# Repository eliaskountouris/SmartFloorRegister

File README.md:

# Smart Floor Register (Vent)

Developed alongside 2 mechanical engineering students. The MEs were responsible for designing the housing while I worked on the controller board. This was a prototype design and as such extra connectors and sensors were added they may not be used in the final version.

The controller board interfaces with 4 different thermocouples, which connect to Op-Amps to magnify the signal.

It also drives 2 motor controls (using I2C) and a servo (using PWM).

Power is driven by either batteries or a usb for debugging. A boost converter is on board to power the motors and servos.

## PCB Image

## Schematics

There is a schematic file (Schematic.pdf) detailing the workings of the controller board.

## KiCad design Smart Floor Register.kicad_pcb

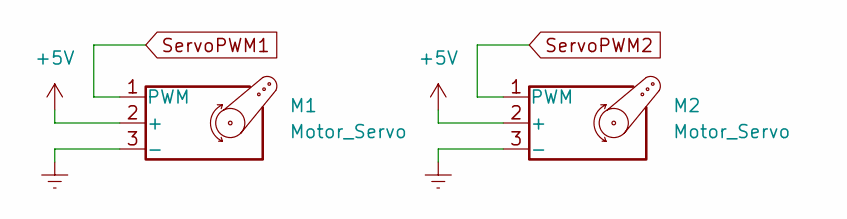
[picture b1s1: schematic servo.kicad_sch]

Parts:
M1, M2: Motor_Servo; Servo

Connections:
+5V: M1.2 (+), M2.2 (+); also elsewhere on the board
Earth: M1.3 (-), M2.3 (-); also elsewhere on the board
ServoPWM1: M1.1 (PWM); also elsewhere on the board
ServoPWM2: M2.1 (PWM); also elsewhere on the board

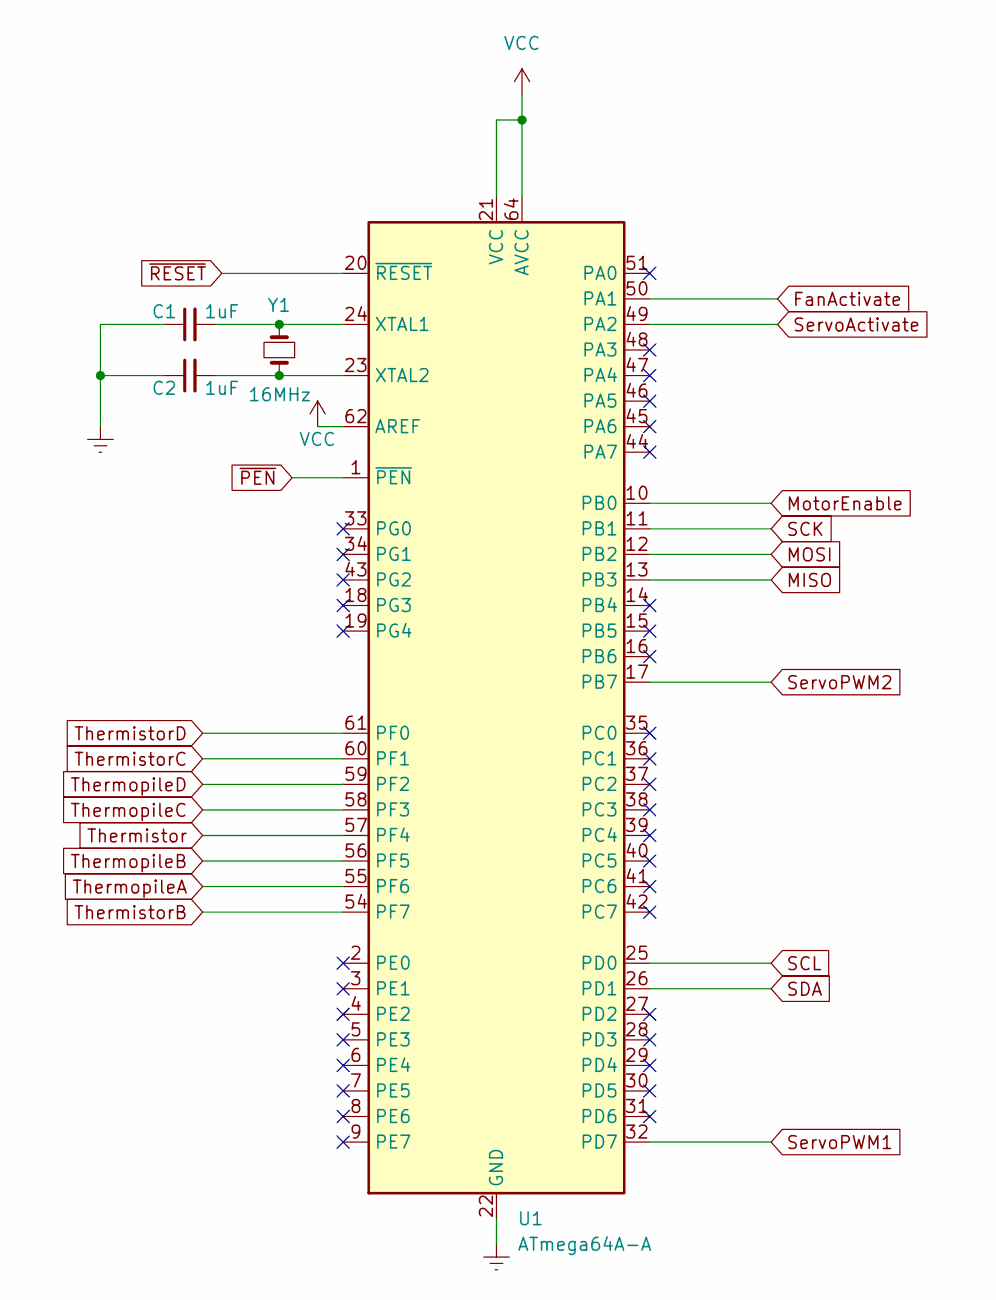
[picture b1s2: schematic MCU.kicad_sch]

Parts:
C1, C2: 1uF; R_0603_1608Metric_Pad0.98x0.95mm_HandSolder
U1: ATmega64A-A; TQFP-64_14x14mm_P0.8mm
Y1: 16MHz; XTAL_ECS-160-S-23A-TR

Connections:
Earth: C1.1, C2.1, U1.22 (GND), U1.53 (GND), U1.63 (GND); also elsewhere on the board
FanActivate: U1.50 (PA1); also elsewhere on the board
MISO: U1.13 (PB3); also elsewhere on the board
MOSI: U1.12 (PB2); also elsewhere on the board
MotorEnable: U1.10 (PB0); also elsewhere on the board
unnamed: C1.2, U1.24 (XTAL1), Y1.2
unnamed: C2.2, U1.23 (XTAL2), Y1.1
SCK: U1.11 (PB1); also elsewhere on the board
SCL: U1.25 (PD0); also elsewhere on the board
SDA: U1.26 (PD1); also elsewhere on the board
ServoActivate: U1.49 (PA2); also elsewhere on the board
ServoPWM1: U1.32 (PD7); also elsewhere on the board
ServoPWM2: U1.17 (PB7); also elsewhere on the board
Thermistor: U1.57 (PF4); also elsewhere on the board
ThermistorB: U1.54 (PF7); also elsewhere on the board
ThermistorC: U1.60 (PF1); also elsewhere on the board
ThermistorD: U1.61 (PF0); also elsewhere on the board
ThermopileA: U1.55 (PF6); also elsewhere on the board
ThermopileB: U1.56 (PF5); also elsewhere on the board
ThermopileC: U1.58 (PF3); also elsewhere on the board
ThermopileD: U1.59 (PF2); also elsewhere on the board
VCC: U1.21 (VCC), U1.52 (VCC), U1.62 (AREF), U1.64 (AVCC); also elsewhere on the board
~PEN: U1.1 (~PEN); also elsewhere on the board
~RESET: U1.20 (~RESET); also elsewhere on the board

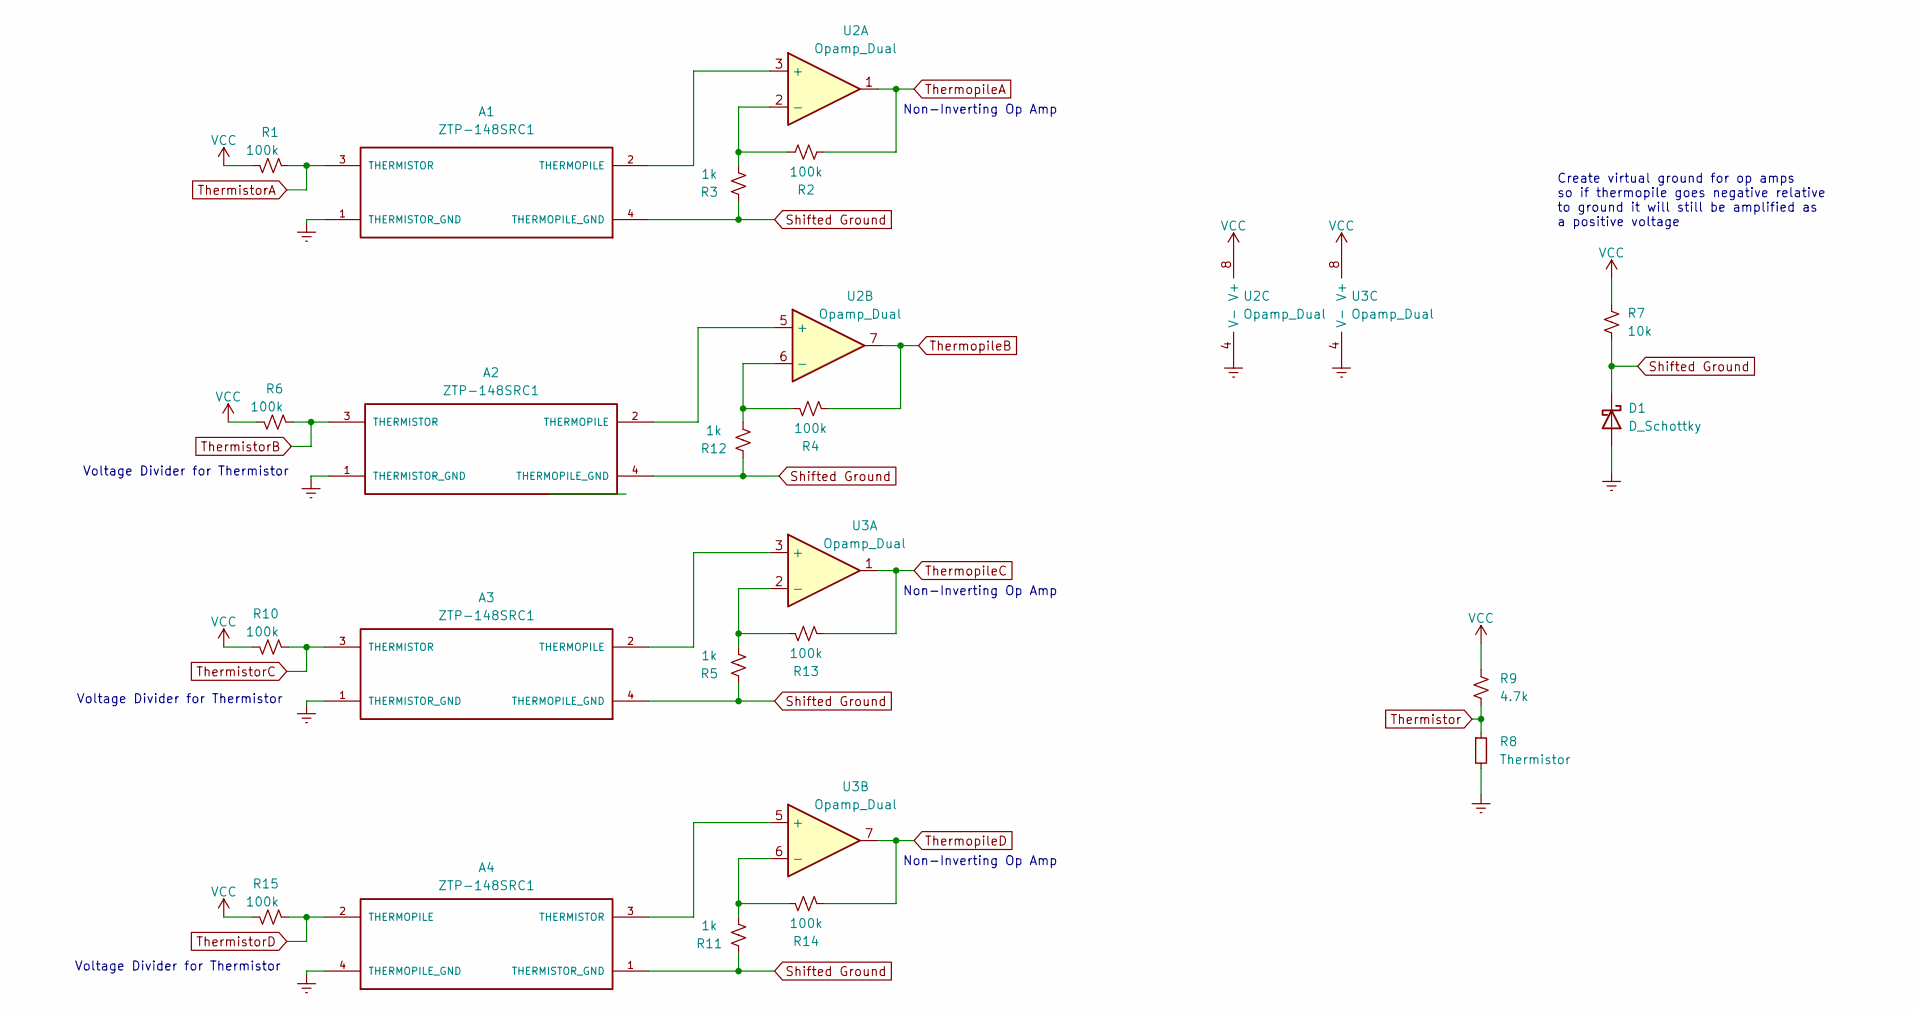
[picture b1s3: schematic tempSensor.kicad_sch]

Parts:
A1, A2, A3, A4: ZTP-148SRC1; Thermopile; PARTREV 07/2020
D1: D_Schottky; D_SOD-323
R1, R2, R4, R6, R10, R13, R14, R15: 100k; R_0603_1608Metric_Pad0.98x0.95mm_HandSolder
R3, R5, R11, R12: 1k; R_0603_1608Metric_Pad0.98x0.95mm_HandSolder
R7: 10k; R_0603_1608Metric_Pad0.98x0.95mm_HandSolder
R8: Thermistor; R_1206_3216Metric_Pad1.30x1.75mm_HandSolder
R9: 4.7k; R_0603_1608Metric_Pad0.98x0.95mm_HandSolder
U2, U3: Opamp_Dual; AD8539ARMZ-REEL

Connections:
Earth: A1.1 (THERMISTOR_GND), A2.1 (THERMISTOR_GND), A3.1 (THERMISTOR_GND), A4.4 (THERMOPILE_GND), D1.2 (A), R8.2, U2.4 (V-), U3.4 (V-); also elsewhere on the board
unnamed: A1.2 (THERMOPILE), U2.3 (+)
unnamed: A2.2 (THERMOPILE), U2.5 (+)
unnamed: A3.2 (THERMOPILE), U3.3 (+)
unnamed: A4.3 (THERMISTOR), U3.5 (+)
unnamed: R2.2, R3.2, U2.2 (-)
unnamed: R4.1, R12.2, U2.6 (-)
unnamed: R5.2, R13.1, U3.2 (-)
unnamed: R11.2, R14.1, U3.6 (-)
Shifted Ground: A1.4 (THERMOPILE_GND), A2.4 (THERMOPILE_GND), A3.4 (THERMOPILE_GND), A4.1 (THERMISTOR_GND), D1.1 (K), R3.1, R5.1, R7.2, R11.1, R12.1; also elsewhere on the board
Thermistor: R8.1, R9.2; also elsewhere on the board
ThermistorA: A1.3 (THERMISTOR), R1.2; also elsewhere on the board
ThermistorB: A2.3 (THERMISTOR), R6.2; also elsewhere on the board
ThermistorC: A3.3 (THERMISTOR), R10.2; also elsewhere on the board
ThermistorD: A4.2 (THERMOPILE), R15.2; also elsewhere on the board
ThermopileA: R2.1, U2.1; also elsewhere on the board
ThermopileB: R4.2, U2.7; also elsewhere on the board
ThermopileC: R13.2, U3.1; also elsewhere on the board
ThermopileD: R14.2, U3.7; also elsewhere on the board
VCC: R1.1, R6.1, R7.1, R9.1, R10.1, R15.1, U2.8 (V+), U3.8 (V+); also elsewhere on the board

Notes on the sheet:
Voltage Divider for Thermistor
Non-Inverting Op Amp
Create virtual ground for op amps so if thermopile goes negative relative to ground it will still be amplified as a positive voltage

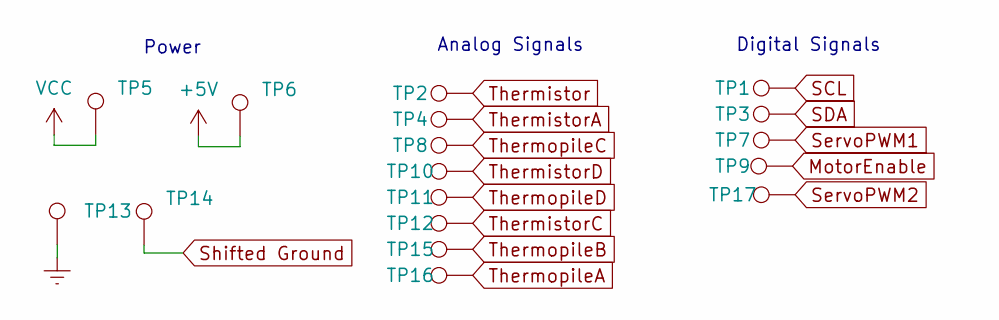
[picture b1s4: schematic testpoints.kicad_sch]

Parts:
TP1, TP2, TP3, TP4, TP5, TP6, TP7, TP8, TP9, TP10, TP11, TP12, TP13, TP14, TP15, TP16, TP17: TestPoint; TestPoint_Pad_D1.5mm

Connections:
+5V: TP6.1; also elsewhere on the board
Earth: TP13.1; also elsewhere on the board
MotorEnable: TP9.1; also elsewhere on the board
SCL: TP1.1; also elsewhere on the board
SDA: TP3.1; also elsewhere on the board
ServoPWM1: TP7.1; also elsewhere on the board
ServoPWM2: TP17.1; also elsewhere on the board
Shifted Ground: TP14.1; also elsewhere on the board
Thermistor: TP2.1; also elsewhere on the board
ThermistorA: TP4.1; also elsewhere on the board
ThermistorC: TP12.1; also elsewhere on the board
ThermistorD: TP10.1; also elsewhere on the board
ThermopileA: TP16.1; also elsewhere on the board
ThermopileB: TP15.1; also elsewhere on the board
ThermopileC: TP8.1; also elsewhere on the board
ThermopileD: TP11.1; also elsewhere on the board
VCC: TP5.1; also elsewhere on the board

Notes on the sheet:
Power
Digital Signals
Analog Signals

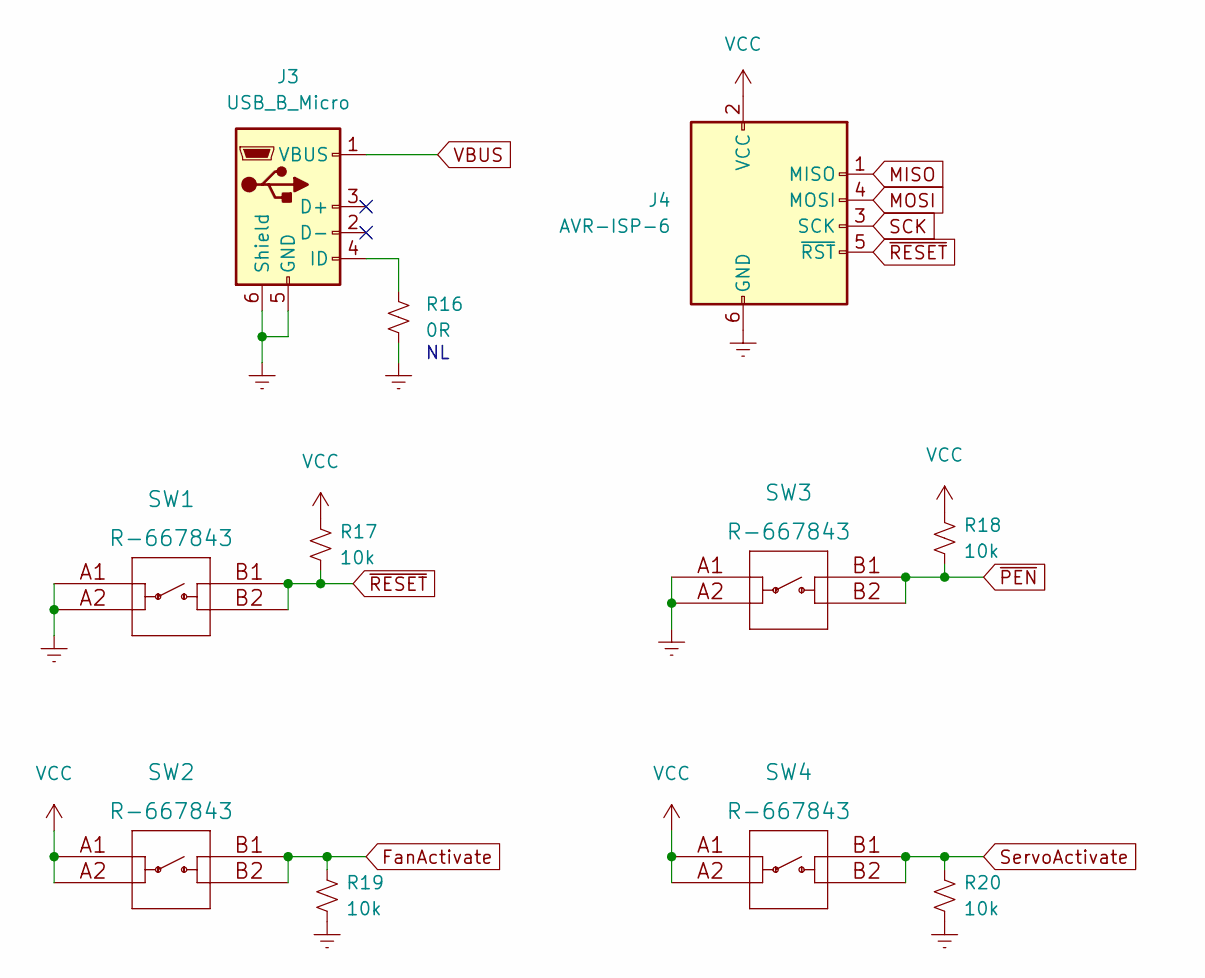
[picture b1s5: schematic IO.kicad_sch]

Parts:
J3: USB_B_Micro; MOLEX_105164-0001
J4: AVR-ISP-6; TSW-103-08-F-D-RA
R16: 0R; R_0603_1608Metric_Pad0.98x0.95mm_HandSolder
R17, R18, R19, R20: 10k; R_0603_1608Metric_Pad0.98x0.95mm_HandSolder
SW1, SW2, SW3, SW4: R-667843

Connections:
Earth: J3.5 (GND), J3.6 (Shield), J4.6 (GND), R16.2, R19.2, R20.2, SW1.A1, SW1.A2, SW3.A1, SW3.A2; also elsewhere on the board
FanActivate: R19.1, SW2.B1, SW2.B2; also elsewhere on the board
MISO: J4.1 (MISO); also elsewhere on the board
MOSI: J4.4 (MOSI); also elsewhere on the board
unnamed: J3.4 (ID), R16.1
SCK: J4.3 (SCK); also elsewhere on the board
ServoActivate: R20.1, SW4.B1, SW4.B2; also elsewhere on the board
VBUS: J3.1 (VBUS); also elsewhere on the board
VCC: J4.2 (VCC), R17.1, R18.1, SW2.A1, SW2.A2, SW4.A1, SW4.A2; also elsewhere on the board
~PEN: R18.2, SW3.B1, SW3.B2; also elsewhere on the board
~RESET: J4.5 (~RST), R17.2, SW1.B1, SW1.B2; also elsewhere on the board

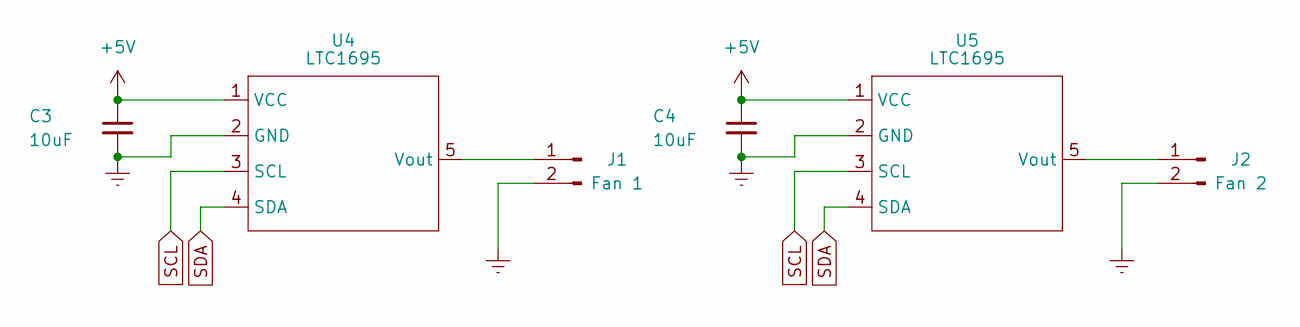
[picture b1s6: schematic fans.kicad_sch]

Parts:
C3, C4: 10uF; R_0603_1608Metric_Pad0.98x0.95mm_HandSolder
J1: Fan 1; Fan
J2: Fan 2; Fan
U4, U5: LTC1695; LTC1695CS5-TRPBF

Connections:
+5V: C3.1, C4.1, U4.1 (VCC), U5.1 (VCC); also elsewhere on the board
Earth: C3.2, C4.2, J1.2, J2.2, U4.2 (GND), U5.2 (GND); also elsewhere on the board
unnamed: J1.1, U4.5 (Vout)
unnamed: J2.1, U5.5 (Vout)
SCL: U4.3 (SCL), U5.3 (SCL); also elsewhere on the board
SDA: U4.4 (SDA), U5.4 (SDA); also elsewhere on the board

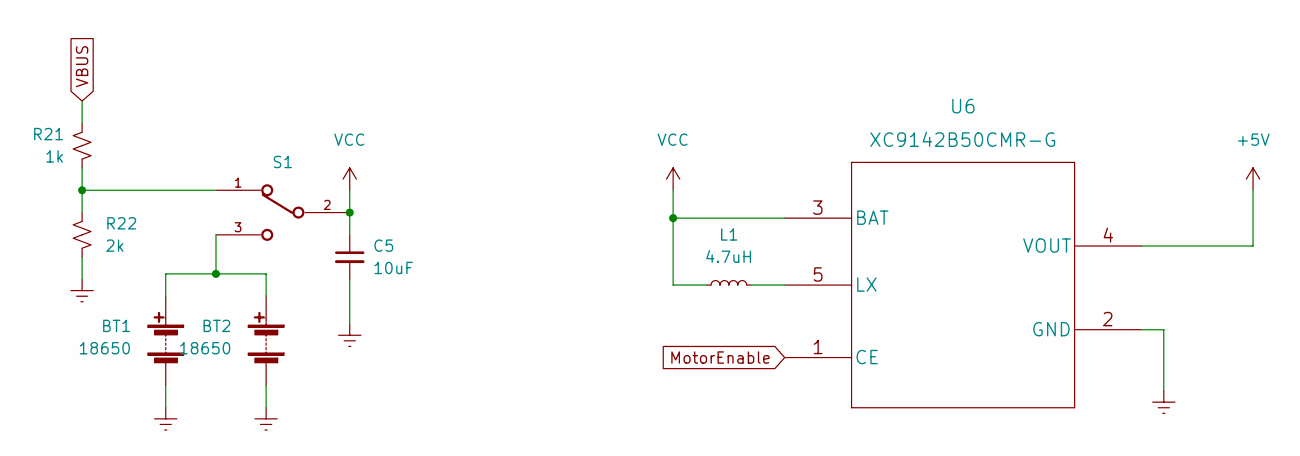
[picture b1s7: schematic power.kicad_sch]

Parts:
BT1, BT2: 18650; 1049P
C5: 10uF; R_0603_1608Metric_Pad0.98x0.95mm_HandSolder
L1: 4.7uH; L_0603_1608Metric_Pad1.05x0.95mm_HandSolder
R21: 1k; R_0603_1608Metric_Pad0.98x0.95mm_HandSolder
R22: 2k; R_0603_1608Metric_Pad0.98x0.95mm_HandSolder
S1: a; SW_JS102011SAQN
U6: XC9142B50CMR-G

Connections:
+5V: U6.4 (VOUT); also elsewhere on the board
Earth: BT1.2 (-), BT2.2 (-), C5.2, R22.2, U6.2 (GND); also elsewhere on the board
MotorEnable: U6.1 (CE); also elsewhere on the board
unnamed: BT1.1 (+), BT2.1 (+), S1.3
unnamed: L1.2, U6.5 (LX)
unnamed: R21.2, R22.1, S1.1
VBUS: R21.1; also elsewhere on the board
VCC: C5.1, L1.1, S1.2, U6.3 (BAT); also elsewhere on the board

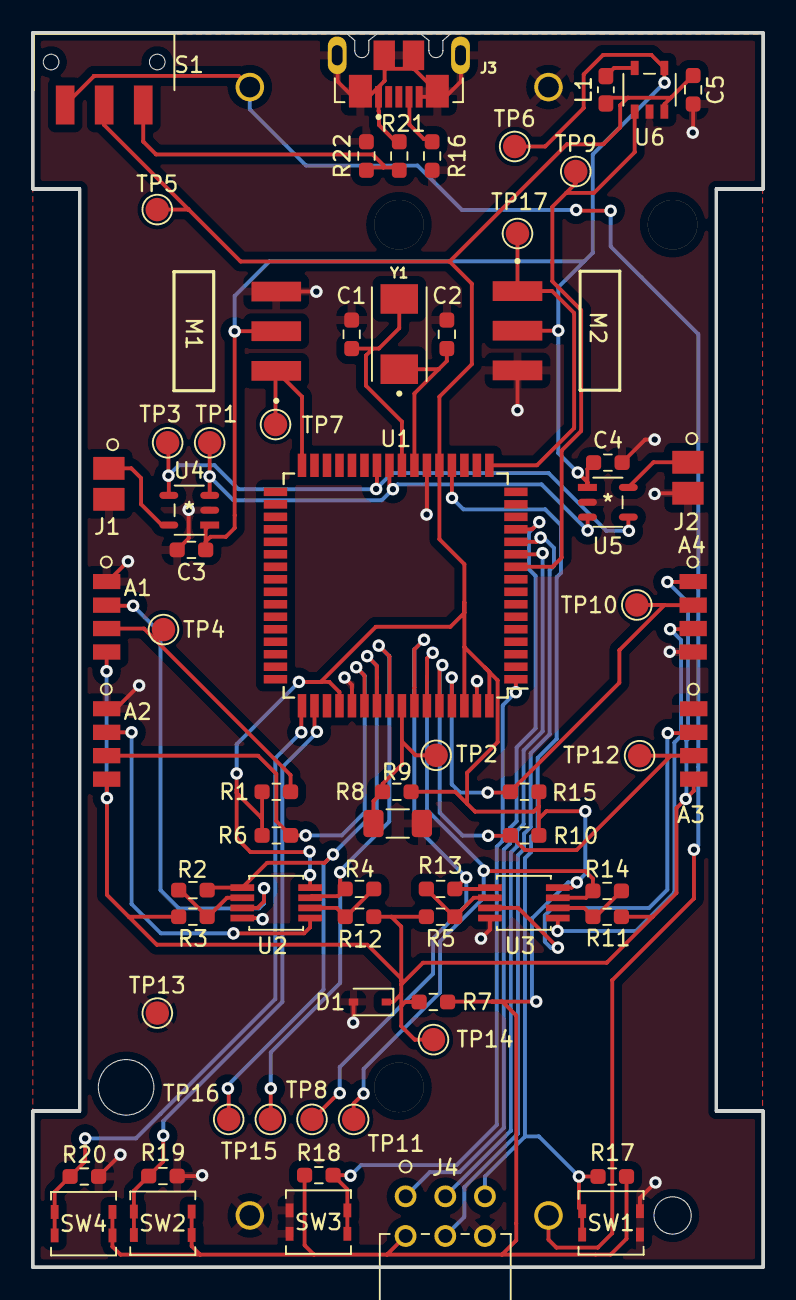
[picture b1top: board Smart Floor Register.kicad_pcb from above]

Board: 2 copper layers, 46.8 x 79.1 mm, 69 parts (1 on the bottom side), 42 nets.

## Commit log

2022-07-11 init commit
2022-07-11 git ignore
2022-07-11 Selected MCU
2022-07-14 Add MCU circuit
2022-07-15 BOM + Motor Controllers
2022-07-18 Motor Controllers
2022-07-26 Temp Sensors Circuitry
2022-07-26 Reorganized Datasheets
2022-07-27 Power + Servo
2022-08-01 Changed MCU
2022-08-01 Added Footprints
2022-08-01 Started PCB
2022-08-02 Gerbers
2022-08-02 Added PDF
2022-08-03 Updated Gerbers
2022-08-05 Fixed IR Sensor
2022-08-05 Finalized PCB
2022-09-20 Added Docs
2022-09-21 Image

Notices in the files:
parts and their libraries:
Copyright 2021 Accelerated Designs. All rights reserved.
